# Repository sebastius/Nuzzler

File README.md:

# Nuzzler
A hotend heater for Bambulabs X1C hotends

This version is untested.

Designed with these parts on order:
- https://www.aliexpress.com/item/1005006322355552.html (display)
- https://www.aliexpress.com/item/1005007080333485.html (jst-xh, 2 pin)
- https://www.aliexpress.com/item/1005004337800850.html (jst-gh, 2pin)
- 1k 0805
- 100k 0805
- Arduino Nano
- https://www.aliexpress.com/item/1005006949630465.html (USB C Trigger board, 12v (in theory you could go 20V but the Arduino Nano vreg will burn...))

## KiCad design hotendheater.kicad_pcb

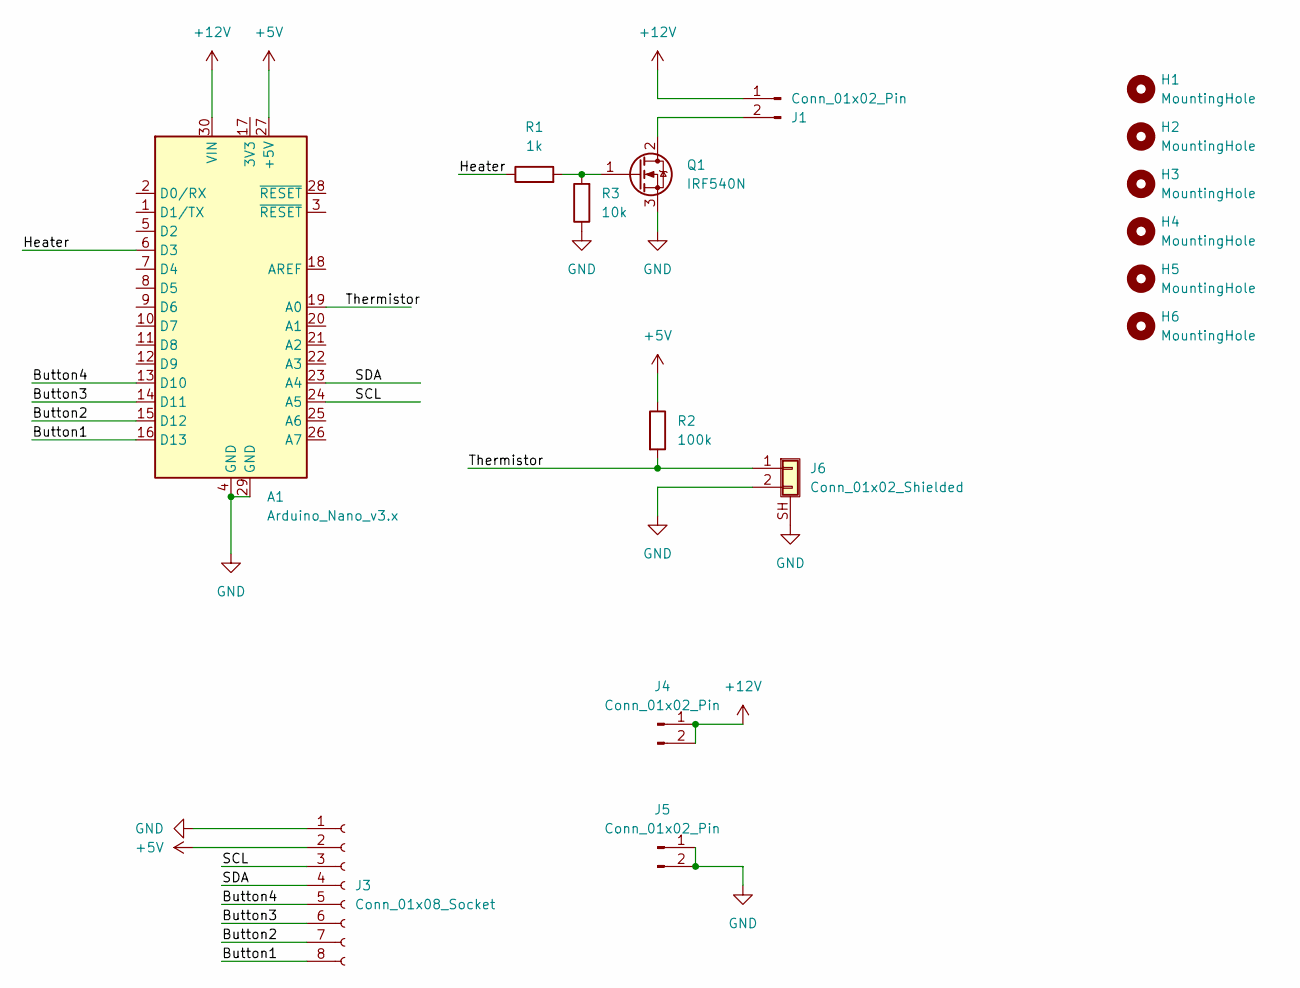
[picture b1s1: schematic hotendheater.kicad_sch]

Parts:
A1: Arduino_Nano_v3.x; Arduino_Nano
H1, H2, H3, H4, H5, H6: MountingHole; MountingHole_3.2mm_M3_DIN965
J1: Conn_01x02_Pin; JST_XH_S2B-XH-A_1x02_P2.50mm_Horizontal
J3: Conn_01x08_Socket; PinHeader_1x08_P2.54mm_Vertical
J4, J5: Conn_01x02_Pin; PinHeader_1x02_P2.54mm_Vertical
J6: Conn_01x02_Shielded; JST_GH_SM02B-GHS-TB_1x02-1MP_P1.25mm_Horizontal
Q1: IRF540N; TO-220-3_Vertical
R1: 1k; R_0805_2012Metric
R2: 100k; R_0805_2012Metric
R3: 10k; R_0805_2012Metric

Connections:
+5V: A1.27 (+5V), J3.2, R2.1
+12V: A1.30 (VIN), J1.1, J4.1, J4.2
/Button1: A1.16 (D13), J3.8
/Button2: A1.15 (D12), J3.7
/Button3: A1.14 (D11), J3.6
/Button4: A1.13 (D10), J3.5
/Heater: A1.6 (D3), R1.1
/SCL: A1.24 (A5), J3.3
/SDA: A1.23 (A4), J3.4
/Thermistor: A1.19 (A0), J6.1, R2.2
GND: A1.4 (GND), A1.29 (GND), J3.1, J5.1, J5.2, J6.2, J6.SH (Shield), Q1.3 (S), R3.1
unnamed: J1.2, Q1.2 (D)
unnamed: Q1.1 (G), R1.2, R3.2

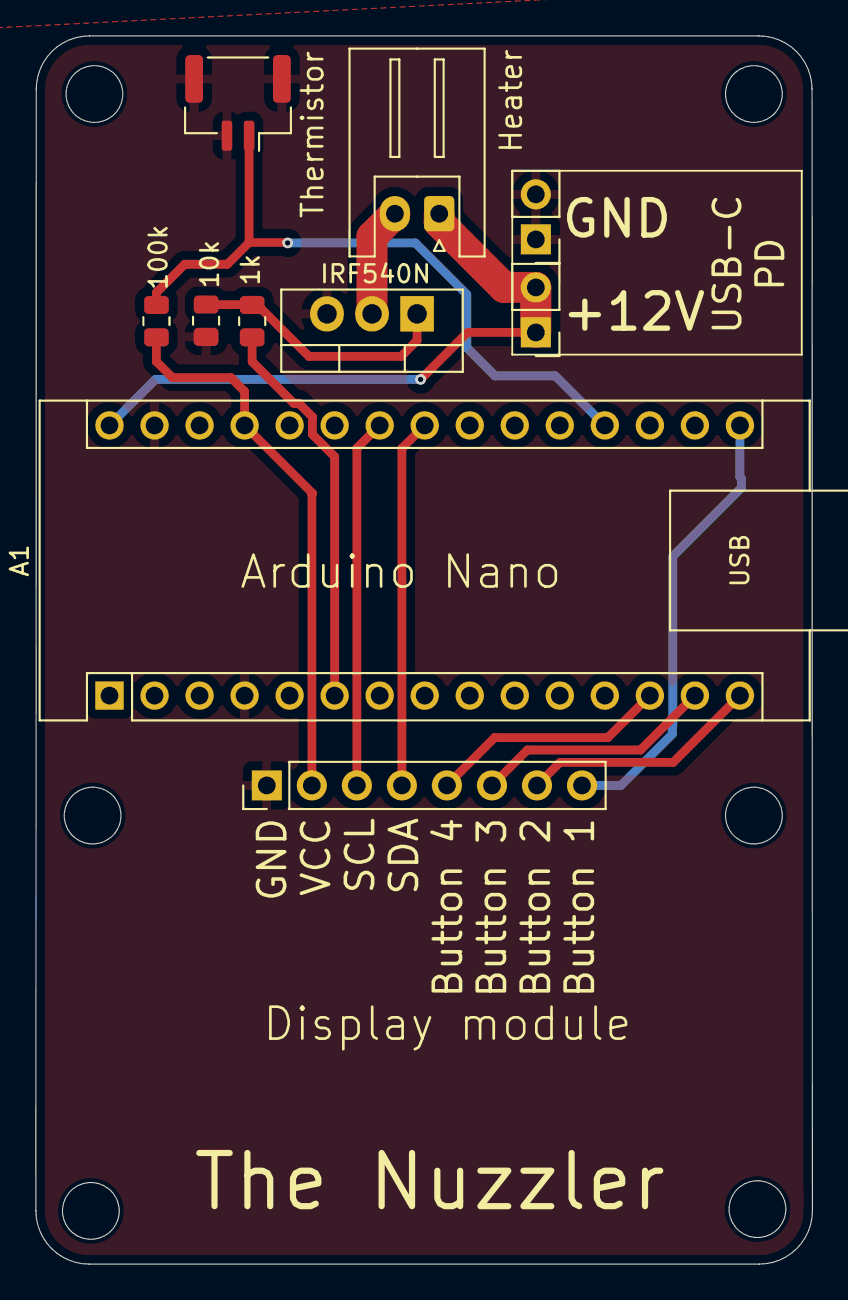
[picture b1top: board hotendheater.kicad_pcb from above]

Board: 2 copper layers, 43.8 x 69.3 mm, 16 parts (0 on the bottom side), 13 nets.

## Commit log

2024-11-29 Add files via upload
    Testversion. Do not make these yourself.
2024-11-29 Improvements
